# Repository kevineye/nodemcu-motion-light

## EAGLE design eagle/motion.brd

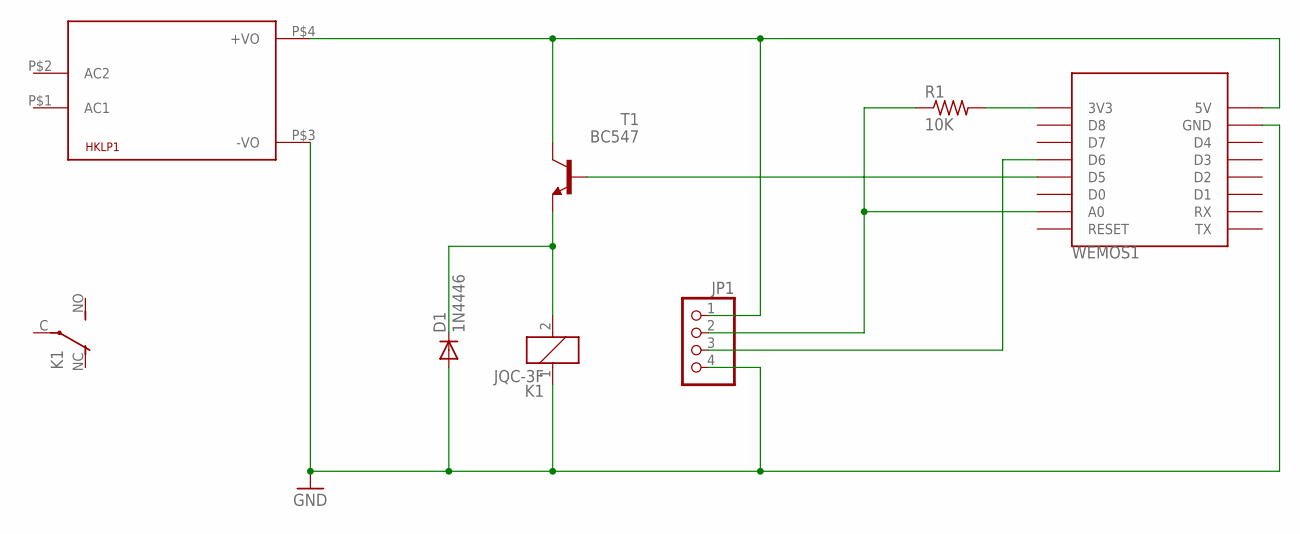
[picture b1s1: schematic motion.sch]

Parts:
D1: 1N4446; DO35-10
HKLP1: HKLPM01
JP1: PINHD-1X4; 1X04
K1: JQC-3F; JS-M
R1: 10K; 0309V
T1: BC547; TO92
WEMOS1: WEMOS-D1-MINI

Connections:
GND: D1.A, HKLP1.P$3 (-VO), JP1.4, K1.1, WEMOS1.GND
unnamed: JP1.3, WEMOS1.D6
unnamed: JP1.2, R1.1, WEMOS1.A0
unnamed: T1.2 (B), WEMOS1.D5
unnamed: R1.2, WEMOS1.3V3
unnamed: HKLP1.P$4 (+VO), JP1.1, T1.3 (C), WEMOS1.5V
unnamed: D1.C, K1.2, T1.1 (E)

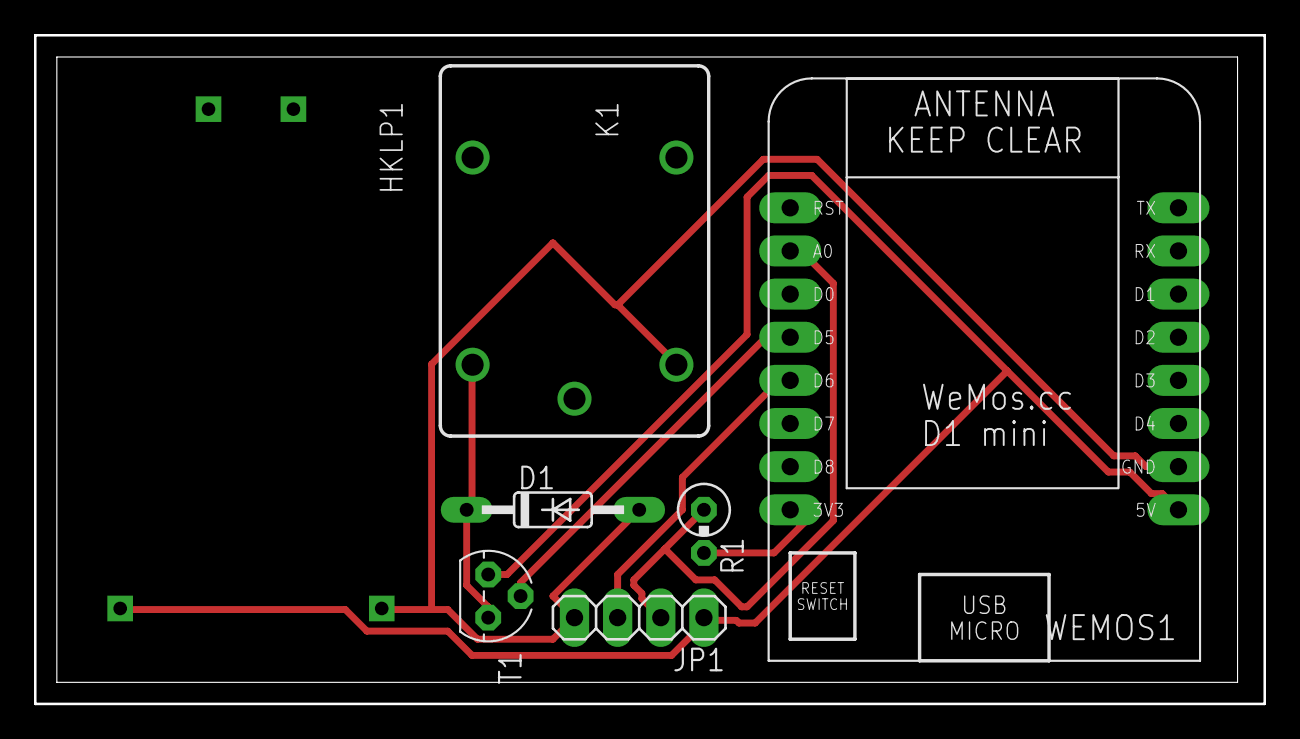
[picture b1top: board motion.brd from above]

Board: 2 copper layers, 72.4 x 39.4 mm, 7 parts (0 on the bottom side), 7 nets.

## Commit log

2017-06-21 initial motion sensor commit
2017-10-01 added delay and light sensing; fixed light reversal
2017-10-02 simplified sensors module
2017-10-02 udpated lib version
2017-10-07 tightened up memory usage
2017-10-07 added eagle files
2017-10-07 added hostname setting
2017-10-08 added eagle pdf
2017-10-08 enlarged pads
